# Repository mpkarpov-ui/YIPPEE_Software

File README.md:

# YIPPEE

**Your Integrated Presicion Positioning (and) Elevation Engine**

### About YIPPEE

YIPPEE is a personal project that I started in early 2025, and was my entry into hardware design, as I was interested in learning more about how my [college rocketry team](https://www.illinoisspacesociety.org/spaceshot) developed the hardware for its flight computers.

After receiving help from our Electronic Hardware lead, I had a schematic and layout I was happy with and produced it in our school's electronic lab. The software for this project was in majority written by me with some key contributions from [Surag Nuthulapaty](https://github.com/SuragNuthulapaty), who is a very smart and cool guy.

### Using YIPPEE

#### Hardware

All hardware schematics are present in `hardware/`. As of August 2025, the RPP diode is no longer being produced or sold, but can just be replaced with a jumper wire.

All components can be sourced commercially through Transfer Multisort Elektronik (TME), DigiKey, Mouser, LCSC, and Amazon.

All hardware schematics are free for use.

#### Software

YIPPEE software is compiled with [Platformio](https://platformio.org/), which offers easy VSCode integration with their extension. The configuration defines 4 targets which are described below:

**hardware_test** – This target suspends all normal functions of the flight computer and pre-empts them by putting in code configured to mass-test the components on the board, this is useful for board assembly and debugging.

**main** - This is the main "flight code" and includes finished drivers, flash memory management system, telemetry code, and a barometer-based flight FSM.

**mem_offload** – This target also pre-empts the main flight code, but instead of testing components, it allows offloading data off the flash memory chip.

**ground** (Feather M0) – Running on a commercial-off-the-shelf radio module (the Feather M0 RFM96), this code can receive YIPPEE radio signals and process them to display live board telemetry on the ground.

To start with your YIPPEE board, connect the USB port on the Teensy 4.0 to any COM port on your computer. Then flash the appropriate target through your Platformio interface of choice.

All YIPPEE software is free to reference.

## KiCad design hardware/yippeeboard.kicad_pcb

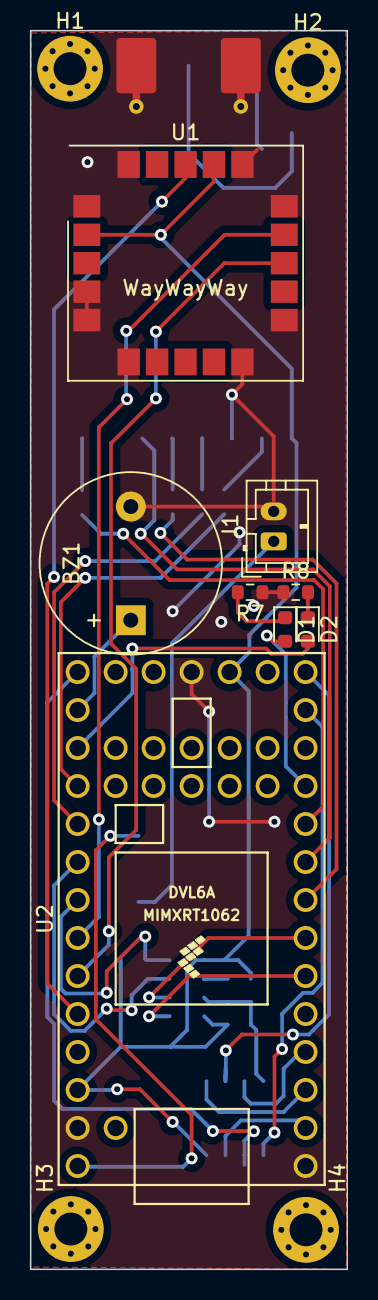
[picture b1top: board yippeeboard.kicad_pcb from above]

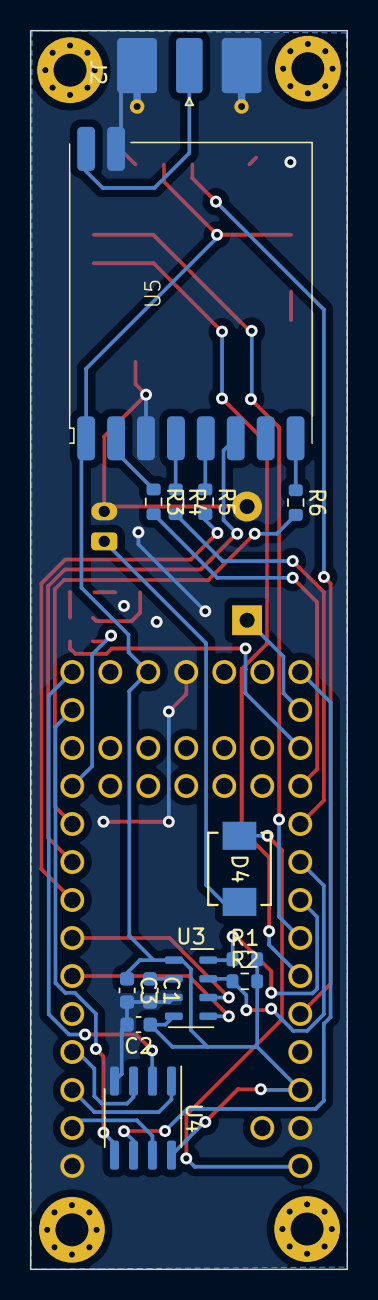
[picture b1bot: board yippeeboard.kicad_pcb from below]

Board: 2 copper layers, 21.2 x 82.8 mm, 26 parts (14 on the bottom side), 33 nets.

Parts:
BZ1: WST-1210; Buzzer_12x9.5RM7.6
C1, C3: 100 nF; C_0603_1608Metric
C2: 10 μF; C_0603_1608Metric
D1: LED_B; LED_0603_1608Metric
D2: LED_G; LED_0603_1608Metric
D4: LSM115JE3/TR13; DO-214BA_MCH
H1, H2, H3, H4: MountingHole_Pad; MountingHole_2.2mm_M2_Pad_Via
J1: Conn_01x02; JST_PH_B2B-PH-K_1x02_P2.00mm_Vertical
J2: Conn_Coaxial; SMA_Molex_73251-2120_EdgeMount_Horizontal
R1, R2: 4.7kΩ; R_0603_1608Metric
R3, R4, R5, R6: 22Ω; R_0603_1608Metric
R7, R8: 470; R_0603_1608Metric
U1: SAM-M10Q; ublox_SAM-M8Q
U2: Teensy4.0; Teensy40
U3: MPL3115A2; NXP_LGA-8_3x5mm_P1.25mm_H1.1mm
U4: SST26VF040A-104I/SN; SOIC-8_3.9x4.9mm_P1.27mm
U5: HM-TRLR-S-433; HM-TRLR-S-xxx

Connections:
+3V3: C2.1, C3.1, R1.2, R2.2, U1.2 (VCC_IO), U1.17 (VCC), U2.16 (3V3), U2.31 (3V3), U3.1 (VDD), U3.4 (VDDIO), U4.8 (VDD), U5.1 (VCC)
/BARO_INT1: U2.7 (5_IN2), U3.6 (INT1)
/BARO_INT2: U2.6 (4_BCLK2), U3.5 (INT2)
/BUZZER_SIG: BZ1.1 (-), U2.21 (14_A0_TX3_SPDIF_OUT)
/GPS_RESET: U1.18 (~RESET), U2.29 (22_A8_CTX1)
/GPS_RX: U1.13 (TXD), U2.28 (21_A7_RX5_BCLK1)
/GPS_TX: U1.14 (RXD), U2.27 (20_A6_TX5_LRCLK1)
/I2C_SCL: R1.1, U2.26 (19_A5_SCL0), U3.8 (SCL)
/I2C_SDA: R2.1, U2.25 (18_A4_SDA0), U3.7 (SDL)
/LED_B: D1.2 (A), U2.11 (9_OUT1C)
/LED_G: D2.2 (A), U2.22 (15_A1_RX3_SPDIF_IN)
/LORA_CONFIG: R5.2, U2.8 (6_OUT1D)
/LORA_RESET: R6.2, U2.10 (8_TX2_IN1)
/LORA_RX: R3.2, U2.23 (16_A2_RX4_SCL1)
/LORA_SLEEP: U2.9 (7_RX2_OUT1A), U5.6 (SLEEP)
/LORA_TX: R4.2, U2.24 (17_A3_TX4_SDA1)
/MEM_CS: U2.3 (1_TX1_CTX2_MISO1), U4.1 (~CE)
/MEM_HOLD: U2.2 (0_RX1_CRX2_CS1), U4.7 (~HOLD)
/MEM_WRITE_PROTECT: U2.4 (2_OUT2), U4.3 (~WP)
/PWR_VIN: D4.1 (K), U2.33 (VIN)
/SPI_MISO: U2.14 (12_MISO_MQSL), U4.2 (SO)
/SPI_MOSI: U2.13 (11_MOSI_CTX1), U4.5 (SI)
/SPI_SCK: U2.20 (13_SCK_CRX1_LED), U4.6 (SCK)
GND: BZ1.2 (+), C1.2, C2.2, C3.2, J1.2, J2.2 (Ext), R7.1, R8.1, U1.1 (GND), U1.4 (GND), U1.5 (GND), U1.6 (GND), U1.10 (GND), U1.11 (GND), U1.15 (GND), U1.16 (GND), U1.20 (GND), U2.1 (GND), U2.17 (GND), U2.32 (GND), U3.3 (GND), U4.4 (VSS), U5.3 (GND), U5.10 (GND)
unnamed: D1.1 (K), R7.2
unnamed: D2.1 (K), R8.2
unnamed: D4.2 (A), J1.1
unnamed: J2.1 (In), U5.9 (ANT)
unnamed: C1.1, U3.2 (CAP)
unnamed: R4.1, U5.4 (RXD)
unnamed: R3.1, U5.2 (TXD)
unnamed: R5.1, U5.5 (~CONFIG)
unnamed: R6.1, U5.8 (~RESET)

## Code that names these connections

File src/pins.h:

#pragma once
// Defines all MCU pins

#define LED_BLUE 9
#define LED_GREEN 15

#define I2C_SDA 18
#define I2C_SCL 19

#define GPS_TX 20
#define GPS_RX 21
#define GPS_RESET 22

#define LORA_TX 17
#define LORA_RX 16
#define LORA_RESET 8
#define LORA_SLEEP 7
#define LORA_CONFIG 6

#define BUZZER 14

#define SCK 13
#define MISO 12
#define MOSI 11

#define MPL311_INT_1 5
#define MPL311_INT_2 4
#define MPL311_ADDR 0x60

#define MEM_WRITE_PROTECT 2
#define MEM_CS 1
#define MEM_HOLD 0

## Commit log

2025-04-28 add stuff
2025-04-29 some things
2025-04-29 asdfasdfasd
2025-04-30 potential flash driver
2025-04-30 more stuff
2025-04-30 stupid workarounnd
2025-04-30 hopehm module add
2025-04-30 mem works
2025-04-30 more rf
2025-04-30 a lot of logger functions
2025-04-30 lora stuff
2025-04-30 full flow ?
2025-05-02 mem offload
2025-05-06 build src fix
2025-05-06 add hardware
2025-08-16 Update docs
